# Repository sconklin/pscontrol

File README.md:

# Control analog interface

This board is designed to connect a programmable power supply with analog control inputs and outputs to a DAQPlate, to enable network control.

# Analog conversions

### Voltage Measurement
Input -5.0V to 0V input represents 600V to 0V
Output 0 to 4.096 to DAQPlate board
Gain = -0.8192
Gain Range .714 - .896

### Current Measurement
Input 0 to 100 mV represents 0 to 1M output
Output 4.096 Volts to DAQplate
Gain = 40.96
Gain Range 38.3 - 43.3

### Voltage Control
Input from DAQplate 0 to 4.096V
Output to Powr Supply 0 to 5 volts
Gain = 1.22
Gain Range 1.098 - 1.294

### Current Limiting Control
Input from DAQplate 0 to 4.096V
Output to Power Supply 0 to 100 mV
Gain = 0.024
Gain Range .0215 - .0261

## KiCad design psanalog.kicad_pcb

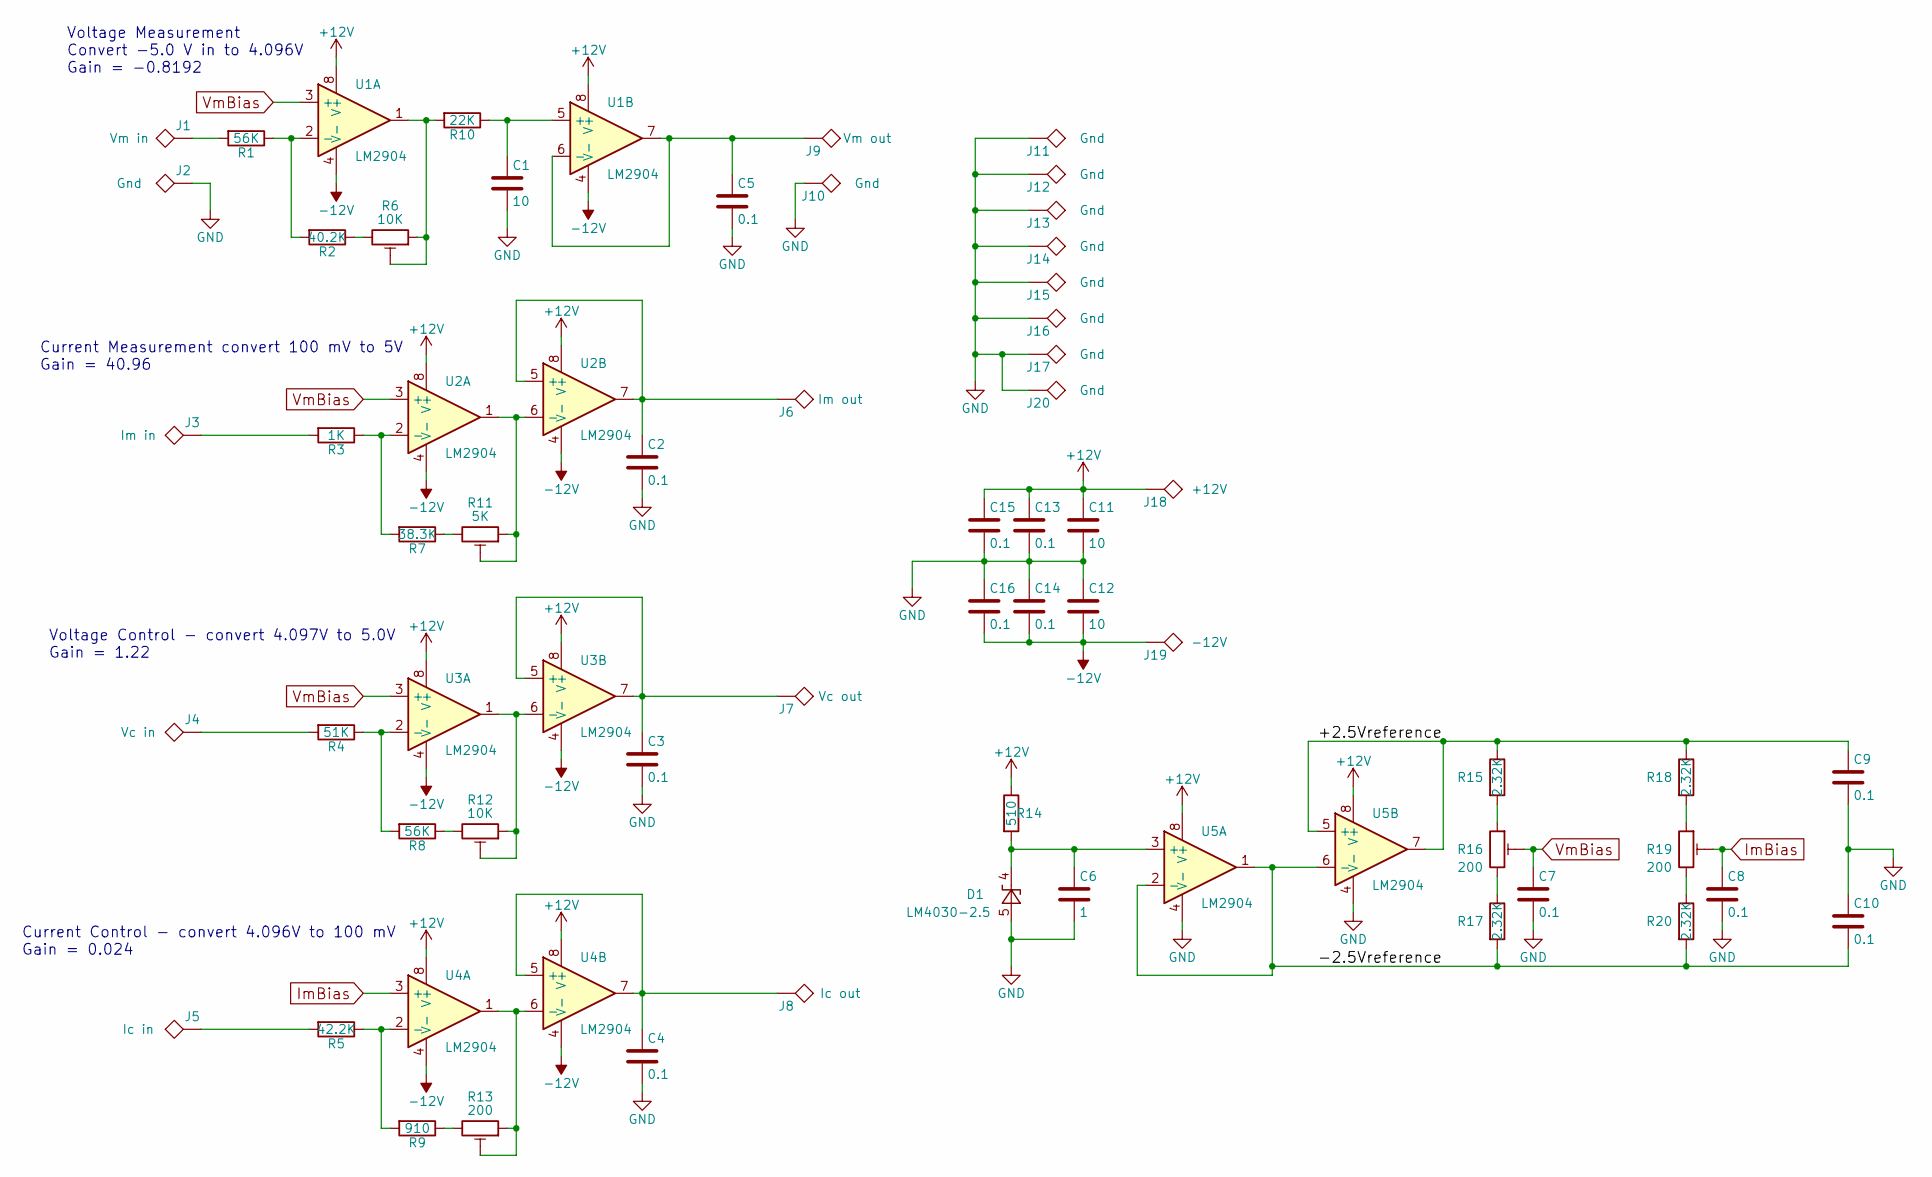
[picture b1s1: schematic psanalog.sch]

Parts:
C1, C11, C12: 10; CP_Elec_4x5.3
C2, C3, C4, C5, C7, C8, C9, C10, C13, C14, C15, C16: 0.1; C_0603_HandSoldering
C6: 1; C_0603_HandSoldering
D1: LM4030-2.5; SOT-23-5
J1: Vm in; SolderWirePad_single_1mmDrill
J2, J10, J11, J12, J13, J14, J15, J16, J17, J20: Gnd; SolderWirePad_single_1mmDrill
J3: Im in; SolderWirePad_single_1mmDrill
J4: Vc in; SolderWirePad_single_1mmDrill
J5: Ic in; SolderWirePad_single_1mmDrill
J6: Im out; SolderWirePad_single_1mmDrill
J7: Vc out; SolderWirePad_single_1mmDrill
J8: Ic out; SolderWirePad_single_1mmDrill
J9: Vm out; SolderWirePad_single_1mmDrill
J18: +12V; SolderWirePad_single_1mmDrill
J19: -12V; SolderWirePad_single_1mmDrill
R1, R8: 56K; R_0603_HandSoldering
R2: 40.2K; R_0603_HandSoldering
R3: 1K; R_0603_HandSoldering
R4: 51K; R_0603_HandSoldering
R5: 42.2K; R_0603_HandSoldering
R6, R12: 10K; Potentiometer_Trimmer_Bourns_3224W
R7: 38.3K; R_0603_HandSoldering
R9: 910; R_0603_HandSoldering
R10: 22K; R_0603_HandSoldering
R11: 5K; Potentiometer_Trimmer_Bourns_3224W
R13, R16, R19: 200; Potentiometer_Trimmer_Bourns_3224W
R14: 510; R_0603_HandSoldering
R15, R17, R18, R20: 2.32K; R_0603_HandSoldering
U1, U2, U3, U4, U5: LM2904; SO-8_5.3x6.2mm_Pitch1.27mm

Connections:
+12V: C11.1, C13.1, C15.1, J18.1, R14.1, U1.8 (V+), U2.8 (V+), U3.8 (V+), U4.8 (V+), U5.8 (V+)
-12V: C12.2, C14.2, C16.2, J19.1, U1.4 (V-), U2.4 (V-), U3.4 (V-), U4.4 (V-)
/+2.5Vreference: C9.1, R15.1, R18.1, U5.5 (+), U5.7
/-2.5Vreference: C10.2, R17.2, R20.2, U5.1, U5.2 (-), U5.6 (-)
GND: C1.2, C2.2, C3.2, C4.2, C5.2, C6.2, C7.2, C8.2, C9.2, C10.1, C11.2, C12.1, C13.2, C14.1, C15.2, C16.1, D1.5 (A), J2.1, J10.1, J11.1, J12.1, J13.1, J14.1, J15.1, J16.1, J17.1, J20.1, U5.4 (V-)
ImBias: C8.1, R19.2, U4.3 (+)
unnamed: C1.1, R10.1, U1.5 (+)
unnamed: C2.1, J6.1, U2.5 (+), U2.7
unnamed: C3.1, J7.1, U3.5 (+), U3.7
unnamed: C4.1, J8.1, U4.5 (+), U4.7
unnamed: C5.1, J9.1, U1.6 (-), U1.7
unnamed: C6.1, D1.4 (K), R14.2, U5.3 (+)
unnamed: J1.1, R1.2
unnamed: J3.1, R3.2
unnamed: J4.1, R4.2
unnamed: J5.1, R5.2
unnamed: R1.1, R2.2, U1.2 (-)
unnamed: R2.1, R6.3
unnamed: R3.1, R7.2, U2.2 (-)
unnamed: R4.1, R8.2, U3.2 (-)
unnamed: R5.1, R9.2, U4.2 (-)
unnamed: R6.1, R6.2, R10.2, U1.1
unnamed: R11.1, R11.2, U2.1, U2.6 (-)
unnamed: R7.1, R11.3
unnamed: R12.1, R12.2, U3.1, U3.6 (-)
unnamed: R8.1, R12.3
unnamed: R13.1, R13.2, U4.1, U4.6 (-)
unnamed: R9.1, R13.3
unnamed: R15.2, R16.1
unnamed: R16.3, R17.1
unnamed: R18.2, R19.1
unnamed: R19.3, R20.1
VmBias: C7.1, R16.2, U1.3 (+), U2.3 (+), U3.3 (+)

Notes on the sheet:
Voltage Control - convert 4.097V to 5.0V Gain = 1.22
Current Control - convert 4.096V to 100 mV Gain = 0.024
Voltage Measurement Convert -5.0 V in to 4.096V Gain = -0.8192
Current Measurement convert 100 mV to 5V Gain = 40.96

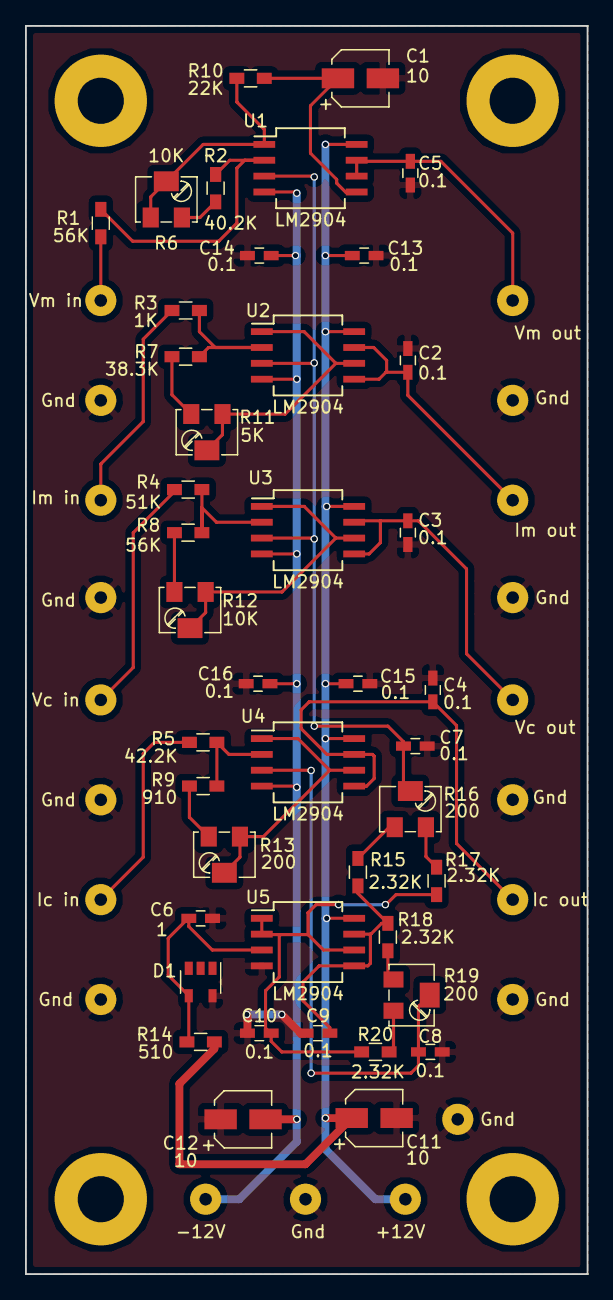
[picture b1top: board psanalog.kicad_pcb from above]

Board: 2 copper layers, 45.0 x 100.0 mm, 62 parts (0 on the bottom side), 33 nets.
